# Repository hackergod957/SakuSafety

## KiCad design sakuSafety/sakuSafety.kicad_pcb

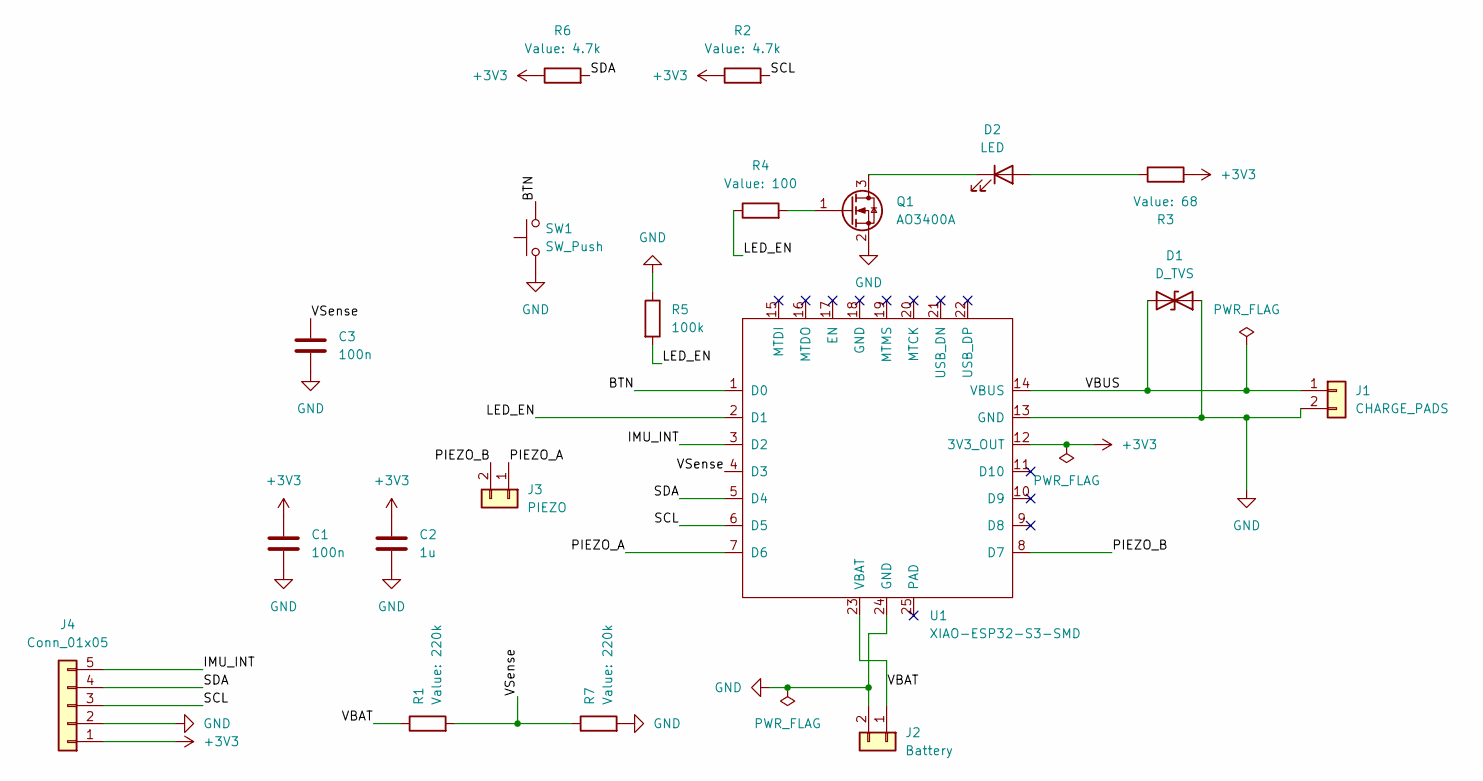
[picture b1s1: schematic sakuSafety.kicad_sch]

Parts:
C1, C3: 100n; C_0603_1608Metric
C2: 1u; C_0603_1608Metric
D1: D_TVS; D_SOD-123
D2: LED; LED_0603_1608Metric
J1: CHARGE_PADS; PinHeader_1x02_P2.54mm_Vertical
J2: Battery; PinHeader_1x02_P2.54mm_Vertical
J3: PIEZO; PinHeader_1x02_P2.54mm_Vertical
J4: Conn_01x05; PinHeader_1x05_P2.54mm_Vertical
Q1: AO3400A; SOT-23
R1, R7: 220k; R_0603_1608Metric
R2, R6: 4.7k; R_0603_1608Metric
R3: 68; R_0603_1608Metric
R4: 100; R_0603_1608Metric
R5: 100k; R_0603_1608Metric
SW1: SW_Push; SW_SPST_PTS810
U1: XIAO-ESP32-S3-SMD

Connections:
+3V3: C1.1, C2.1, J4.1, R2.1, R3.2, R6.1, U1.12 (3V3_OUT)
/BTN: SW1.2, U1.1 (D0)
/IMU_INT: J4.5, U1.3 (D2)
/LED_EN: R4.1, R5.2, U1.2 (D1)
/PIEZO_A: J3.1, U1.7 (D6)
/PIEZO_B: J3.2, U1.8 (D7)
/SCL: J4.3, R2.2, U1.6 (D5)
/SDA: J4.4, R6.2, U1.5 (D4)
/VBAT: J2.1, R1.1, U1.23 (VBAT)
/VBUS: D1.2 (A2), J1.1, U1.14 (VBUS)
/VSense: C3.1, R1.2, R7.1, U1.4 (D3)
GND: C1.2, C2.2, C3.2, D1.1 (A1), J1.2, J2.2, J4.2, Q1.2 (S), R5.1, R7.2, SW1.1, U1.13 (GND), U1.24 (GND)
unnamed: D2.2 (A), R3.1
unnamed: D2.1 (K), Q1.3 (D)
unnamed: Q1.1 (G), R4.2

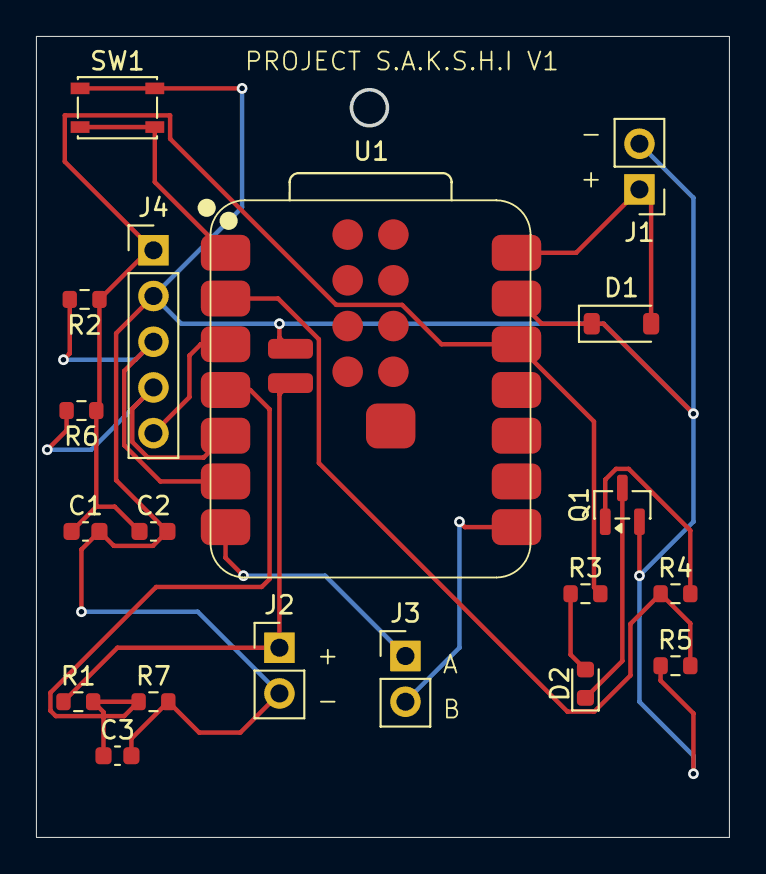
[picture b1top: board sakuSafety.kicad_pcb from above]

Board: 2 copper layers, 38.5 x 44.5 mm, 19 parts (0 on the bottom side), 15 nets.
